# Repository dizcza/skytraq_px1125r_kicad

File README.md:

# SkyTraq PX1125R RTK Kicad design files

Kicad v8.0.

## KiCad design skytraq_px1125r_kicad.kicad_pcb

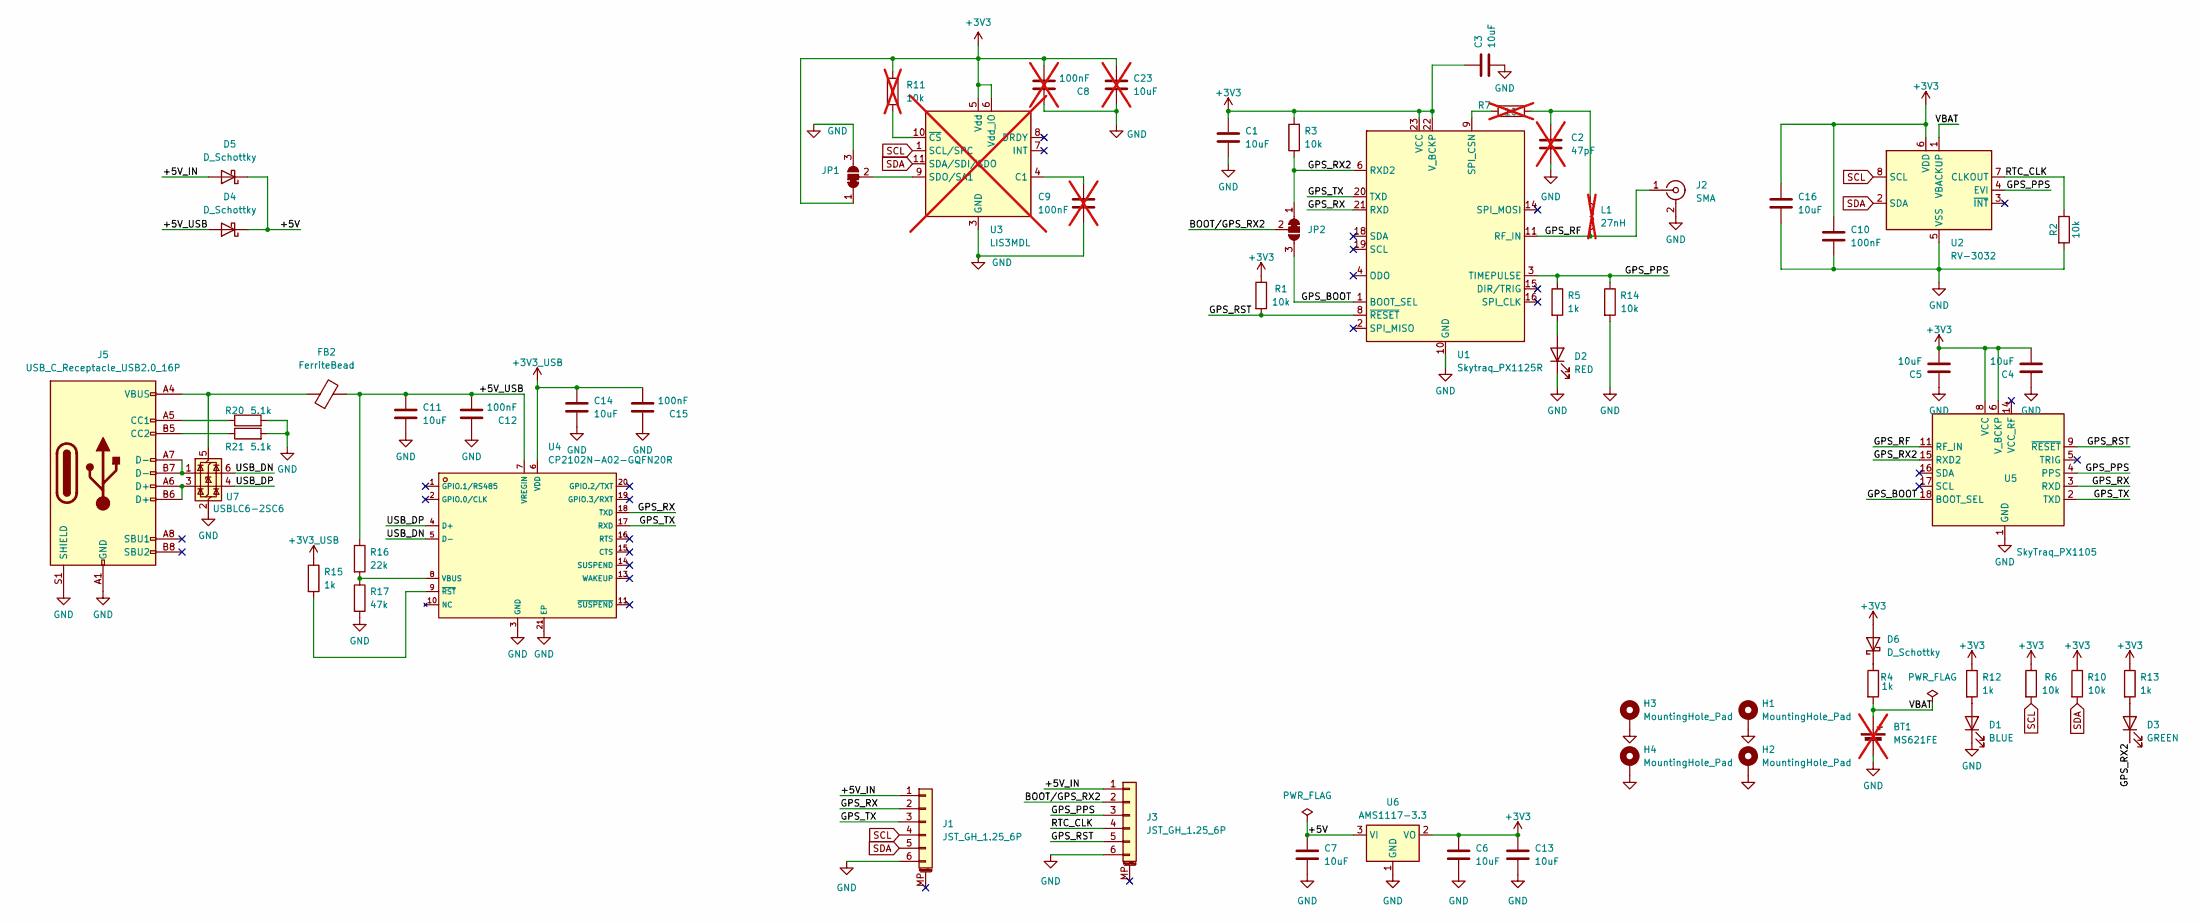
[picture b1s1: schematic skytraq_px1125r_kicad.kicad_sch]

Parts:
BT1: MS621FE; BatteryHolder_Seiko_MS621F; LCSC C80909; not fitted
C1, C3, C4, C5, C6, C7, C11, C13, C14, C16: 10uF; C_0603_1608Metric; LCSC C2959727
C2: 47pF; C_0805_2012Metric_Pad1.18x1.45mm_HandSolder; not fitted
C8, C9: 100nF; C_0402_1005Metric; LCSC C71629; not fitted
C10, C12, C15: 100nF; C_0402_1005Metric; LCSC C71629
C23: 10uF; C_0603_1608Metric; LCSC C2959727; not fitted
D1: BLUE; LED_0603_1608Metric; LCSC C7496819
D2: RED; LED_0603_1608Metric; LCSC C2286
D3: GREEN; LED_0603_1608Metric; LCSC C916074
D4, D5, D6: D_Schottky; D_SOD-323; LCSC C7380001
FB2: FerriteBead; L_0805_2012Metric; LCSC C15957
H1, H2, H3, H4: MountingHole_Pad; MountingHole_3.2mm_M3_Pad
J1, J3: JST_GH_1.25_6P; JST_GH_SM06B-GHS-TB_1x06-1MP_P1.25mm_Horizontal; LCSC C3029381
J2: SMA; SMA-SMD_BWSMA-KE-P001; LCSC C496550
J5: USB_C_Receptacle_USB2.0_16P; USB-C_SMD-TYPE-C-31-M-12_1; LCSC C165948
JP1, JP2: SolderJumper_3_Bridged12; SolderJumper-3_P1.3mm_Bridged12_RoundedPad1.0x1.5mm
L1: 27nH; L_0603_1608Metric; LCSC C12100; not fitted
R1, R2, R3, R6, R10, R14: 10k; R_0402_1005Metric; LCSC C25744
R4, R5, R12, R13, R15: 1k; R_0402_1005Metric; LCSC C11702
R7: 10; R_0805_2012Metric_Pad1.20x1.40mm_HandSolder; not fitted
R11: 10k; R_0402_1005Metric; LCSC C25744; not fitted
R16: 22k; R_0402_1005Metric; LCSC C25768
R17: 47k; R_0402_1005Metric; LCSC C25792
R20, R21: 5.1k; R_0402_1005Metric; LCSC C25905
U1: Skytraq_PX1125R; ublox_NEO
U2: RV-3032; LCSC C5127802
U3: LIS3MDL; LGA-12_L2.0-W2.0-P0.50-BL; LCSC C478483; not fitted
U4: CP2102N-A02-GQFN20R; QFN-20_L3.0-W3.0-P0.50-BL-EP1.7_EFM8BB21F16G; LCSC C969913
U5: SkyTraq_PX1105; skytraq_px1105
U6: AMS1117-3.3; SOT-89-3; LCSC C880752
U7: USBLC6-2SC6; SOT-23-6; LCSC C7519

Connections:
+3V3: C1.1, C3.1, C4.2, C5.2, C6.2, C8.1, C10.1, C13.2, C16.1, C23.2, D6.2 (A), JP1.1 (A), R1.1, R3.2, R6.1, R10.1, R11.2, R12.1, R13.1, U1.22 (V_BCKP), U1.23 (VCC), U2.6 (VDD), U3.5 (Vdd), U3.6 (Vdd_IO), U5.6 (V_BCKP), U5.8 (VCC), U6.2 (VO)
+3V3_USB: C14.2, C15.1, R15.1, U4.6 (VDD)
/+5V: C7.2, D4.1 (K), D5.1 (K), U6.3 (VI)
/+5V_IN: D5.2 (A), J1.1, J3.1
/+5V_USB: C11.2, C12.1, D4.2 (A), FB2.2, R16.1, U4.7 (VREGIN)
/BOOT/GPS_RX2: J3.2, JP2.2 (C)
/GPS_BOOT: JP2.3 (B), U1.1 (BOOT_SEL), U5.18 (BOOT_SEL)
/GPS_PPS: J3.3, R5.1, R14.1, U1.3 (TIMEPULSE), U2.4 (EVI), U5.4 (PPS)
/GPS_RF: J2.1 (In), L1.2, U1.11 (RF_IN), U5.11 (RF_IN)
/GPS_RST: J3.5, R1.2, U1.8 (~RESET), U5.9 (~RESET)
/GPS_RX: J1.2, U1.21 (RXD), U4.18 (TXD), U5.3 (RXD)
/GPS_RX2: D3.1 (K), JP2.1 (A), R3.1, U1.6 (RXD2), U5.15 (RXD2)
/GPS_TX: J1.3, U1.20 (TXD), U4.17 (RXD), U5.2 (TXD)
/RTC_CLK: J3.4, R2.1, U2.7 (CLKOUT)
/USB_DN: U4.5 (D-), U7.6 (I/O1)
/USB_DP: U4.4 (D+), U7.4 (I/O2)
/VBAT: BT1.1 (+), R4.2, U2.1 (VBACKUP)
GND: BT1.2 (-), C1.2, C2.2, C3.2, C4.1, C5.1, C6.1, C7.1, C8.2, C9.1, C10.2, C11.1, C12.2, C13.1, C14.1, C15.2, C16.2, C23.1, D1.1 (K), D2.1 (K), H1.1, H2.1, H3.1, H4.1, J1.6, J2.2 (Ext), J3.6, J5.A1 (GND), J5.A12 (GND), J5.B1 (GND), J5.B12 (GND), J5.S1 (SHIELD), JP1.3 (B), R2.2, R14.2, R17.2, R20.2, R21.2, U1.10 (GND), U1.12 (GND), U1.13 (GND), U1.24 (GND), U2.5 (VSS), U3.2 (GND), U3.3 (GND), U3.12 (GND), U4.3 (GND), U4.12 (GND), U4.21 (EP), U5.1 (GND), U6.1 (GND), U7.2 (GND)
unnamed: C2.1, L1.1, R7.2
unnamed: D1.2 (A), R12.2
unnamed: D2.2 (A), R5.2
unnamed: D3.2 (A), R13.2
unnamed: D6.1 (K), R4.1
unnamed: J5.A5 (CC1), R20.1
unnamed: J5.B5 (CC2), R21.1
unnamed: J5.A6 (D+), J5.B6 (D+), U7.3 (I/O2)
unnamed: J5.A7 (D-), J5.B7 (D-), U7.1 (I/O1)
unnamed: JP1.2 (C), U3.9 (SDO/SA1)
unnamed: R7.1, U1.9 (SPI_CSN)
unnamed: C9.2, U3.4 (C1)
unnamed: R11.1, U3.10 (~CS)
unnamed: R16.2, R17.1, U4.8 (VBUS)
unnamed: R15.2, U4.9 (~RST)
unnamed: FB2.1, J5.A4 (VBUS), J5.A9 (VBUS), J5.B4 (VBUS), J5.B9 (VBUS), U7.5 (VBUS)
SCL: J1.4, R6.2, U2.8 (SCL), U3.1 (SCL/SPC)
SDA: J1.5, R10.2, U2.2 (SDA), U3.11 (SDA/SDI/SDO)

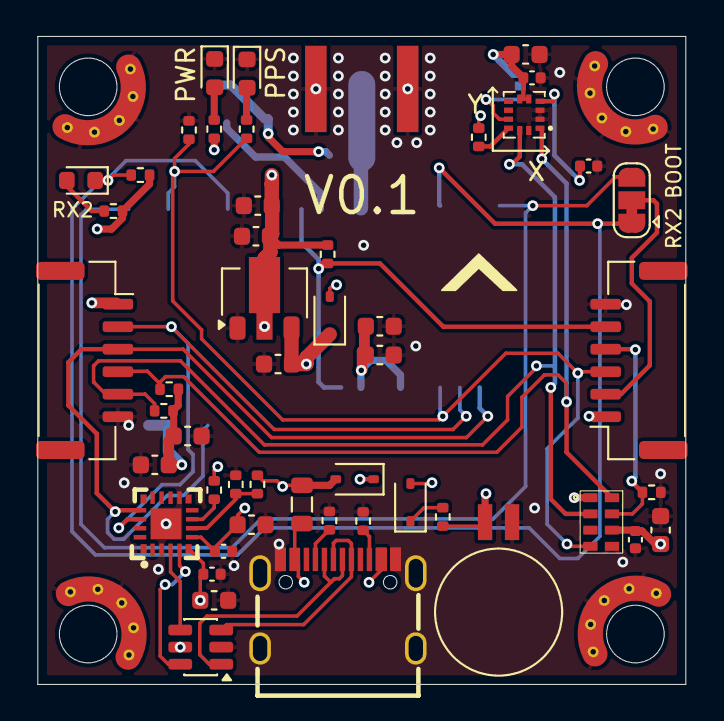
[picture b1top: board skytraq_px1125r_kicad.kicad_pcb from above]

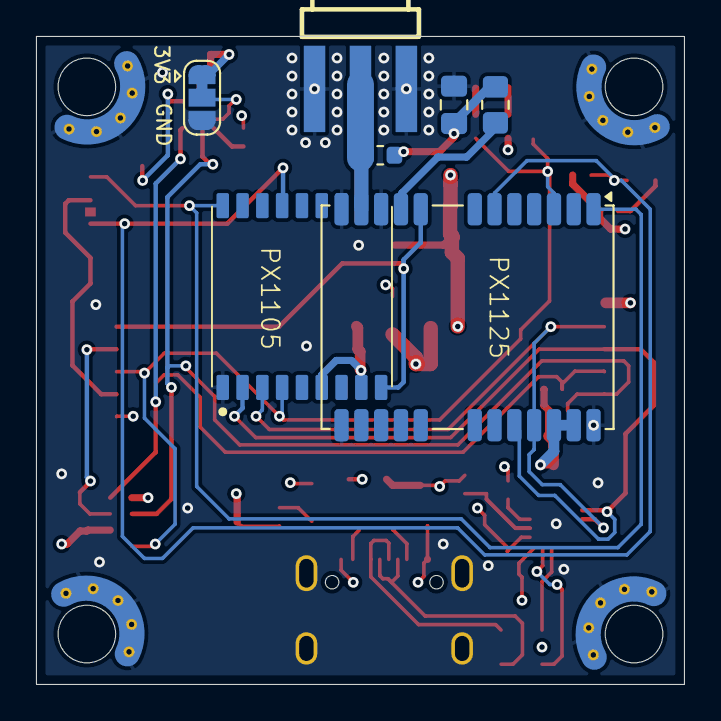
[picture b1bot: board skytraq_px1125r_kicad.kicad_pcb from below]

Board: 4 copper layers, 36.0 x 36.0 mm, 60 parts (7 on the bottom side), 36 nets.

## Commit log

2024-05-12 Done
2025-10-27 PX1105
2025-11-17 36x36 flight controller board
2025-11-18 with px1105 unfinished
2025-11-18 px1105 4-layers boar
2025-11-24 added 2 M3 mounting holes
2025-11-25 one more M3 hole
2026-02-08 36x36 for flight controllers
2026-03-15 added silk arrow
